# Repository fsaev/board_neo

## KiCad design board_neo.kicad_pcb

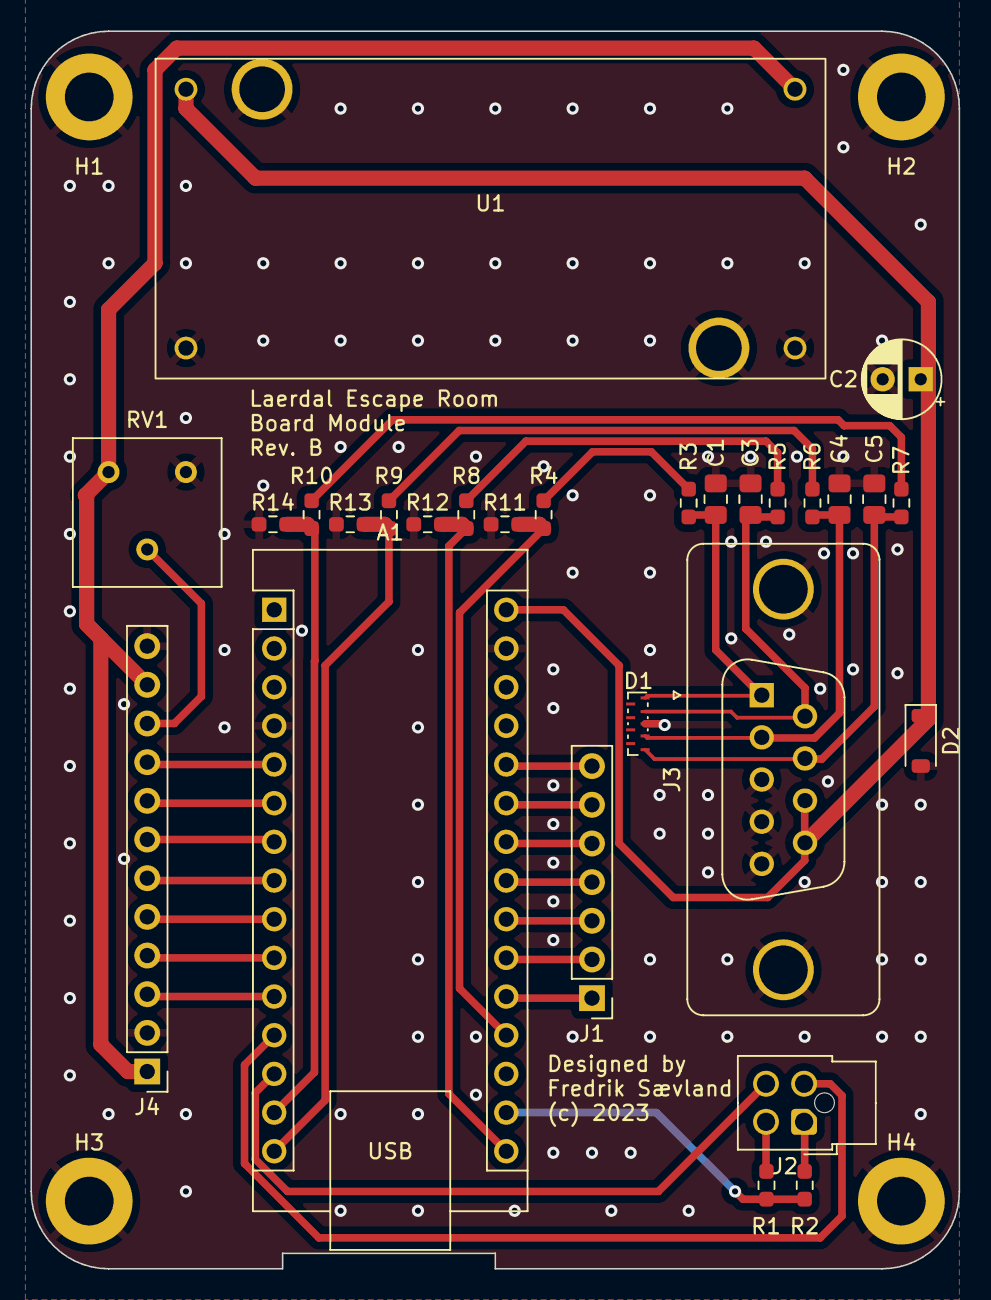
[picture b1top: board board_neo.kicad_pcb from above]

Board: 2 copper layers, 61.0 x 81.3 mm, 32 parts (0 on the bottom side), 35 nets.

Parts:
A1: Arduino_Nano_v3.x; Arduino_Nano
C1, C3, C4, C5: 1nF; C_0805_2012Metric_Pad1.18x1.45mm_HandSolder
C2: C_Polarized_Small; CP_Radial_D5.0mm_P2.50mm
D1: SP7538P; UDFN-9_1.0x3.8mm_P0.5mm
D2: D_Small; D_SOD-123
H1, H2, H3, H4: MountingHole_Pad; MountingHole_3.2mm_M3_ISO7380_Pad
J1: Conn_01x07; PinHeader_1x07_P2.54mm_Vertical
J2: Conn_02x02_Odd_Even; Molex_Nano-Fit_105310-xx04_2x02_P2.50mm_Vertical
J3: DE9_Receptacle_MountingHoles; DSUB-9_Female_Vertical_P2.77x2.84mm_MountingHoles
J4: Conn_01x12; PinHeader_1x12_P2.54mm_Vertical
R1, R2: R_Small; R_0603_1608Metric_Pad0.98x0.95mm_HandSolder
R3, R5, R6, R7: 470R; R_0603_1608Metric_Pad0.98x0.95mm_HandSolder
R4, R8, R9, R10: 11k; R_0603_1608Metric_Pad0.98x0.95mm_HandSolder
R11, R12, R13, R14: 22k; R_0603_1608Metric_Pad0.98x0.95mm_HandSolder
RV1: R_Potentiometer_Small; Potentiometer_Bourns_3386F_Vertical
U1: LM2596_DCDC_dboard

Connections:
3v3: A1.17 (3V3), R1.1, R2.1
Earth: A1.4 (GND), A1.29 (GND), C1.2, C2.2, C3.2, C4.2, C5.2, D1.3 (A), D2.2 (A), H1.1, H2.1, H3.1, H4.1, J3.0 (PAD), J3.3, J3.4, J3.5, J4.2, J4.12, R11.1, R12.1, R13.1, R14.1, RV1.3, U1.1 (mthole_pad1), U1.2 (mthole_pad2), U1.4 (in-), U1.6 (out-)
unnamed: A1.19 (A0), R4.1, R11.2
unnamed: A1.20 (A1), J1.1
unnamed: A1.21 (A2), J1.2
unnamed: A1.22 (A3), J1.3
unnamed: A1.23 (A4), J1.4
unnamed: A1.24 (A5), J1.5
unnamed: A1.25 (A6), J1.6
unnamed: A1.26 (A7), J1.7
unnamed: A1.5 (D2), J4.9
unnamed: A1.6 (D3), J4.8
unnamed: A1.7 (D4), J4.7
unnamed: A1.8 (D5), J4.6
unnamed: A1.9 (D6), J4.5
unnamed: A1.10 (D7), J4.4
unnamed: A1.11 (D8), J4.3
unnamed: A1.12 (D9), J2.2
unnamed: A1.13 (D10), J2.4
unnamed: A1.14 (D11), R10.1, R14.2
unnamed: A1.15 (D12), R9.1, R13.2
unnamed: A1.16 (D13), R8.1, R12.2
unnamed: C5.1, D1.1 (K1), J3.7, R7.1
unnamed: C4.1, D1.2 (K2), J3.2, R6.1
unnamed: C3.1, D1.4 (K3), J3.6, R5.1
unnamed: C1.1, D1.5 (K4), J3.1, R3.1
unnamed: J2.1, R2.2
unnamed: J2.3, R1.2
unnamed: J4.10, RV1.2
unnamed: R3.2, R4.2
unnamed: R5.2, R8.2
unnamed: R6.2, R9.2
unnamed: R7.2, R10.2
VBUCK: J4.1, J4.11, RV1.1, U1.5 (out+)
VIN: A1.30 (VIN), C2.1, D2.1 (K), J3.8, J3.9, U1.3 (in+)

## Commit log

2023-08-07 Finalize design

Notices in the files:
board_neo.kicad_pcb:
(c) 2023
